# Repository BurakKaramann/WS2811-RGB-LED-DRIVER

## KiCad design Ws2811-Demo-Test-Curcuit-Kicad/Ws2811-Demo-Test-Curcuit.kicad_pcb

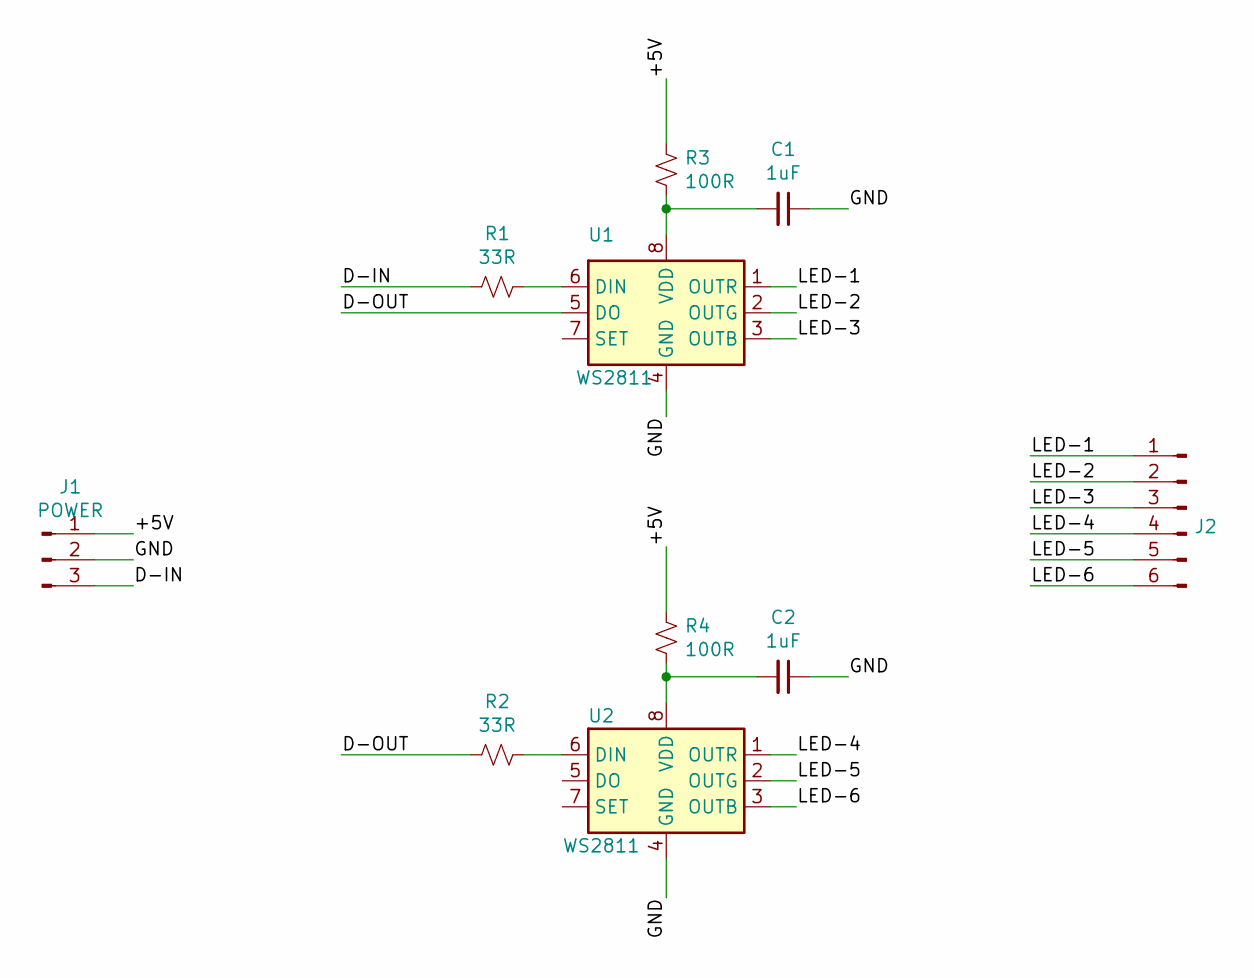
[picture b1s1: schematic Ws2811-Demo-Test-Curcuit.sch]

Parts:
C1, C2: 1uF; C_0805_2012Metric
J1: POWER; PinHeader_1x03_P2.54mm_Vertical
J2: Conn_01x06_Male; PinHeader_1x06_P2.54mm_Vertical
R1, R2: 33R; R_0805_2012Metric
R3, R4: 100R; R_Axial_DIN0309_L9.0mm_D3.2mm_P12.70mm_Horizontal
U1, U2: WS2811; SOP-8_3.76x4.96mm_P1.27mm

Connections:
/+5V: J1.1, R3.1, R4.1
/D-IN: J1.3, R1.2
/D-OUT: R2.2, U1.5 (DO)
/GND: C1.1, C2.1, J1.2, U1.4 (GND), U2.4 (GND)
/LED-1: J2.1, U1.1 (OUTR)
/LED-2: J2.2, U1.2 (OUTG)
/LED-3: J2.3, U1.3 (OUTB)
/LED-4: J2.4, U2.1 (OUTR)
/LED-5: J2.5, U2.2 (OUTG)
/LED-6: J2.6, U2.3 (OUTB)
unnamed: C1.2, R3.2, U1.8 (VDD)
unnamed: C2.2, R4.2, U2.8 (VDD)
unnamed: R1.1, U1.6 (DIN)
unnamed: R2.1, U2.6 (DIN)

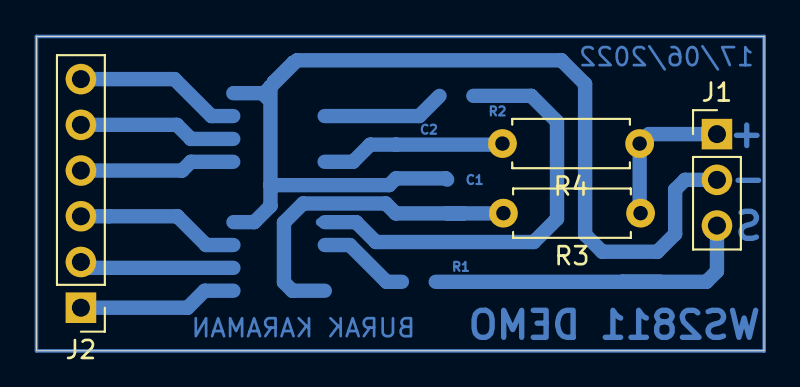
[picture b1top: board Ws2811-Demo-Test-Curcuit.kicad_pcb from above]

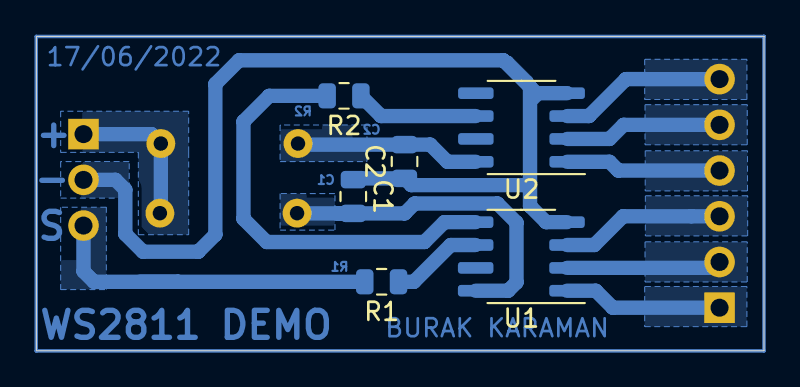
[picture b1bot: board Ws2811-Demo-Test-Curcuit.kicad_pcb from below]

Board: 2 copper layers, 40.4 x 17.5 mm, 10 parts (6 on the bottom side), 14 nets.

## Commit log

2022-06-26 Create KiCad
2022-06-26 Create ArduinoKod
2022-06-26 .
    .
